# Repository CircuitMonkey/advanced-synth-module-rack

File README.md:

# advanced-synth-module-rack
ASMR -- Advanced Synth Module Rack System.  A modern alternative to Eurorack.

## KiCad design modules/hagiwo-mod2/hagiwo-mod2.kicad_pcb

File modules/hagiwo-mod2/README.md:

# Hagiwo Mod2 -- module for ASMR
This module is based on the highly versatile [Mod2 design](https://note.com/solder_state/n/nce8f7defcf98) by Japanese engineer "[Hagiwo](https://note.com/solder_state)".  The Mod2 can operate as a VCO, but can be programmed to masquerade as many types of dedicated drum instruments. This ASMR module is derived from the EuroRack version of their module.

## About
The Unison is based on the Arduino compatible RaspberryPi RP2350 chip. Here, we use the [Raspberry Pi Pico 2 - RP2350](https://www.adafruit.com/product/6006) processor module. Amazingly, it is touted as having a total BOM cost of about $9 in prototype form. Another benefit of the RP2350 based Mod2 module is that experimenters can study and modify the open source code that generates the functionality of the module.

## What is ASMR?
[ASMR -- Advanced Synth Module Rack System](https://github.com/CircuitMonkey/advanced-synth-module-rack).  A modern alternative to Eurorack.

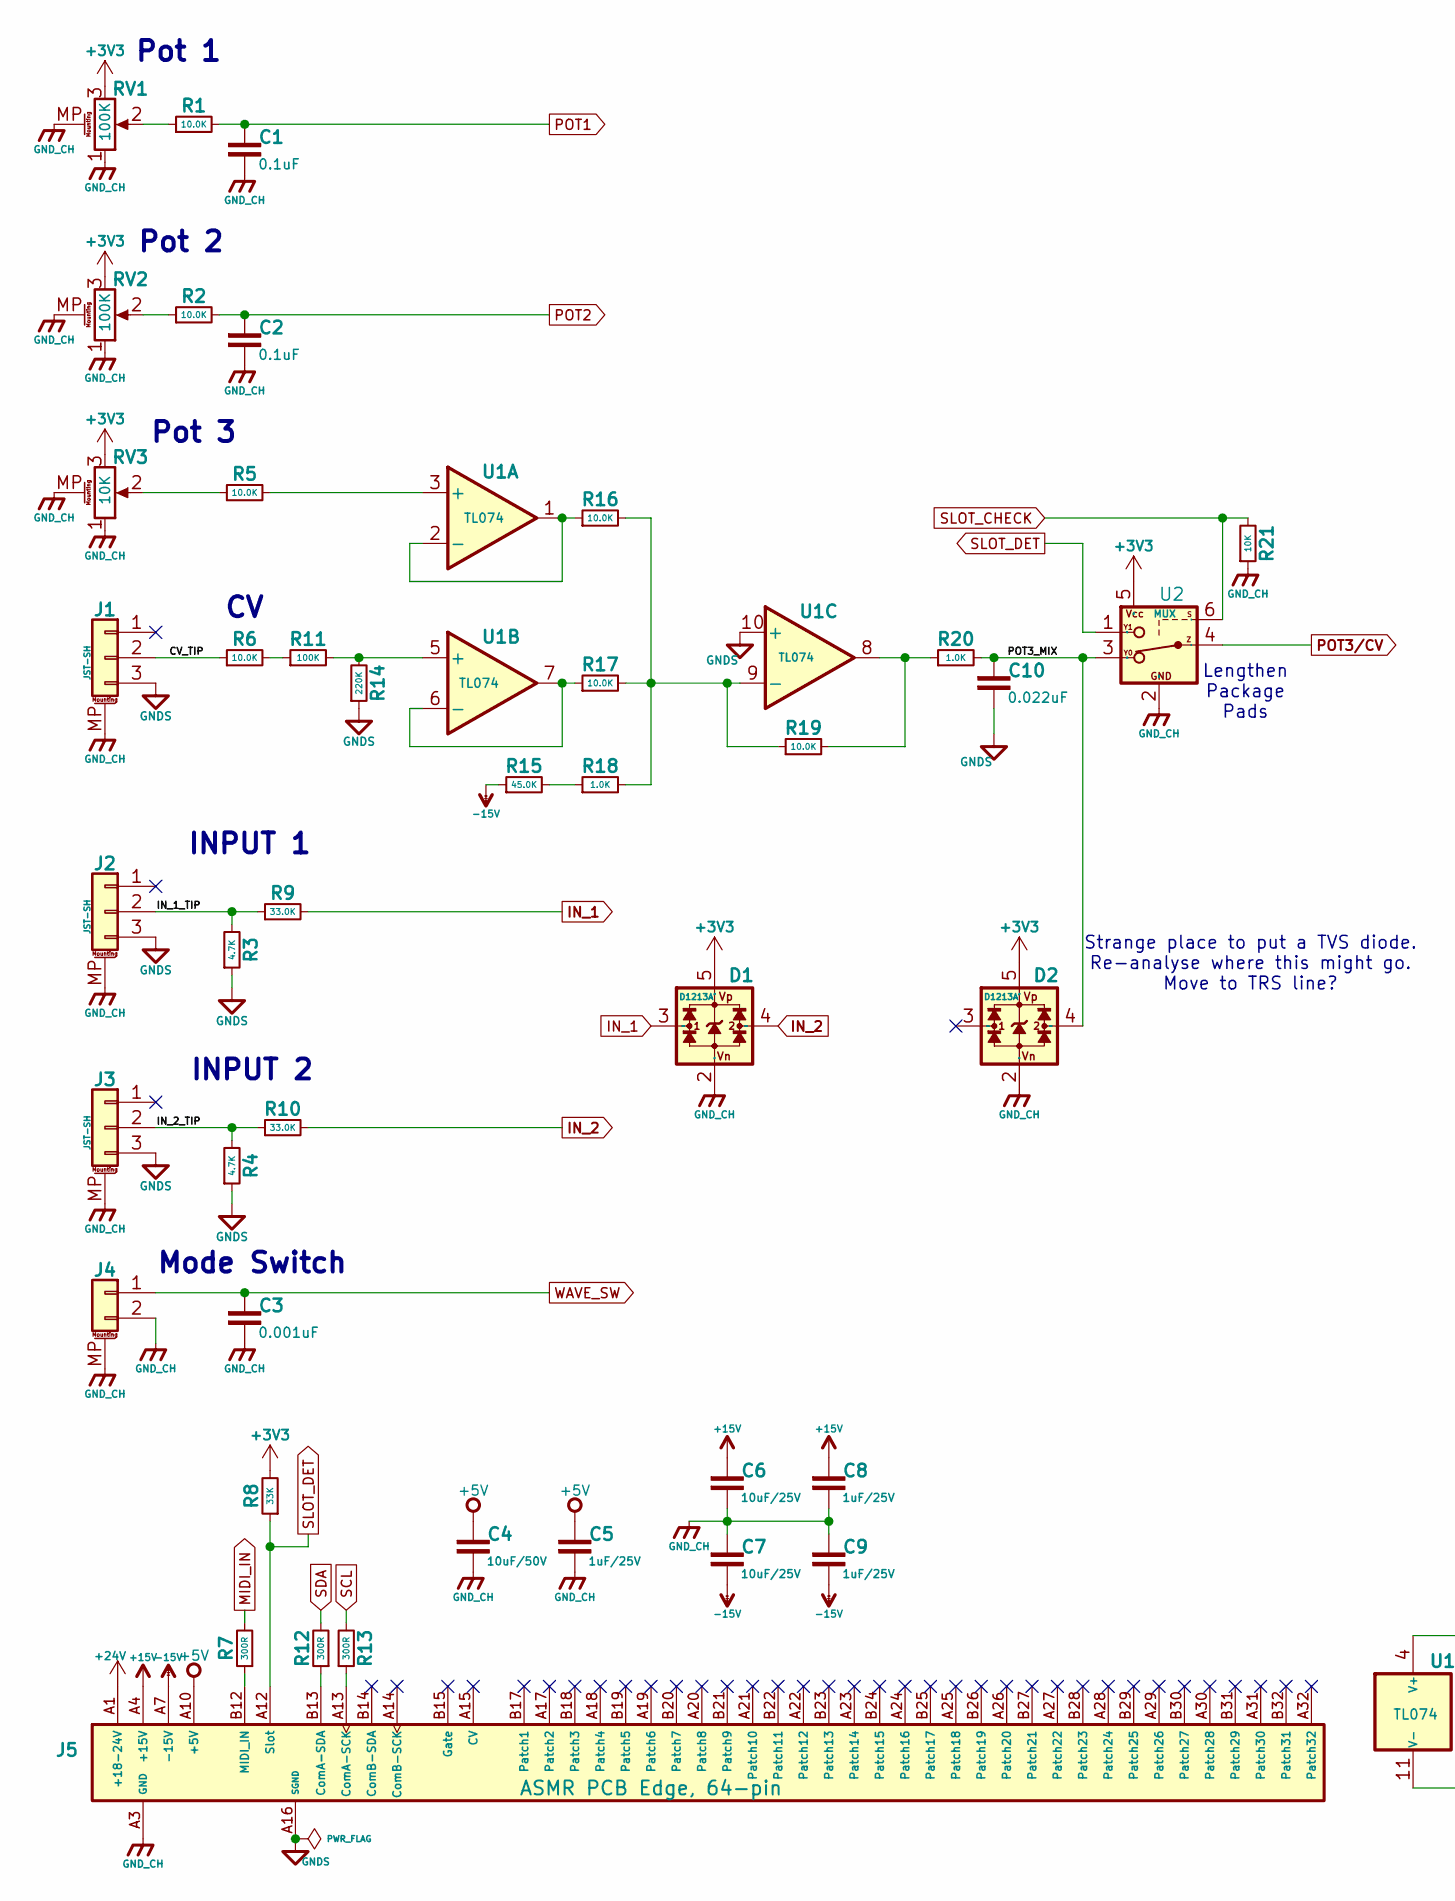
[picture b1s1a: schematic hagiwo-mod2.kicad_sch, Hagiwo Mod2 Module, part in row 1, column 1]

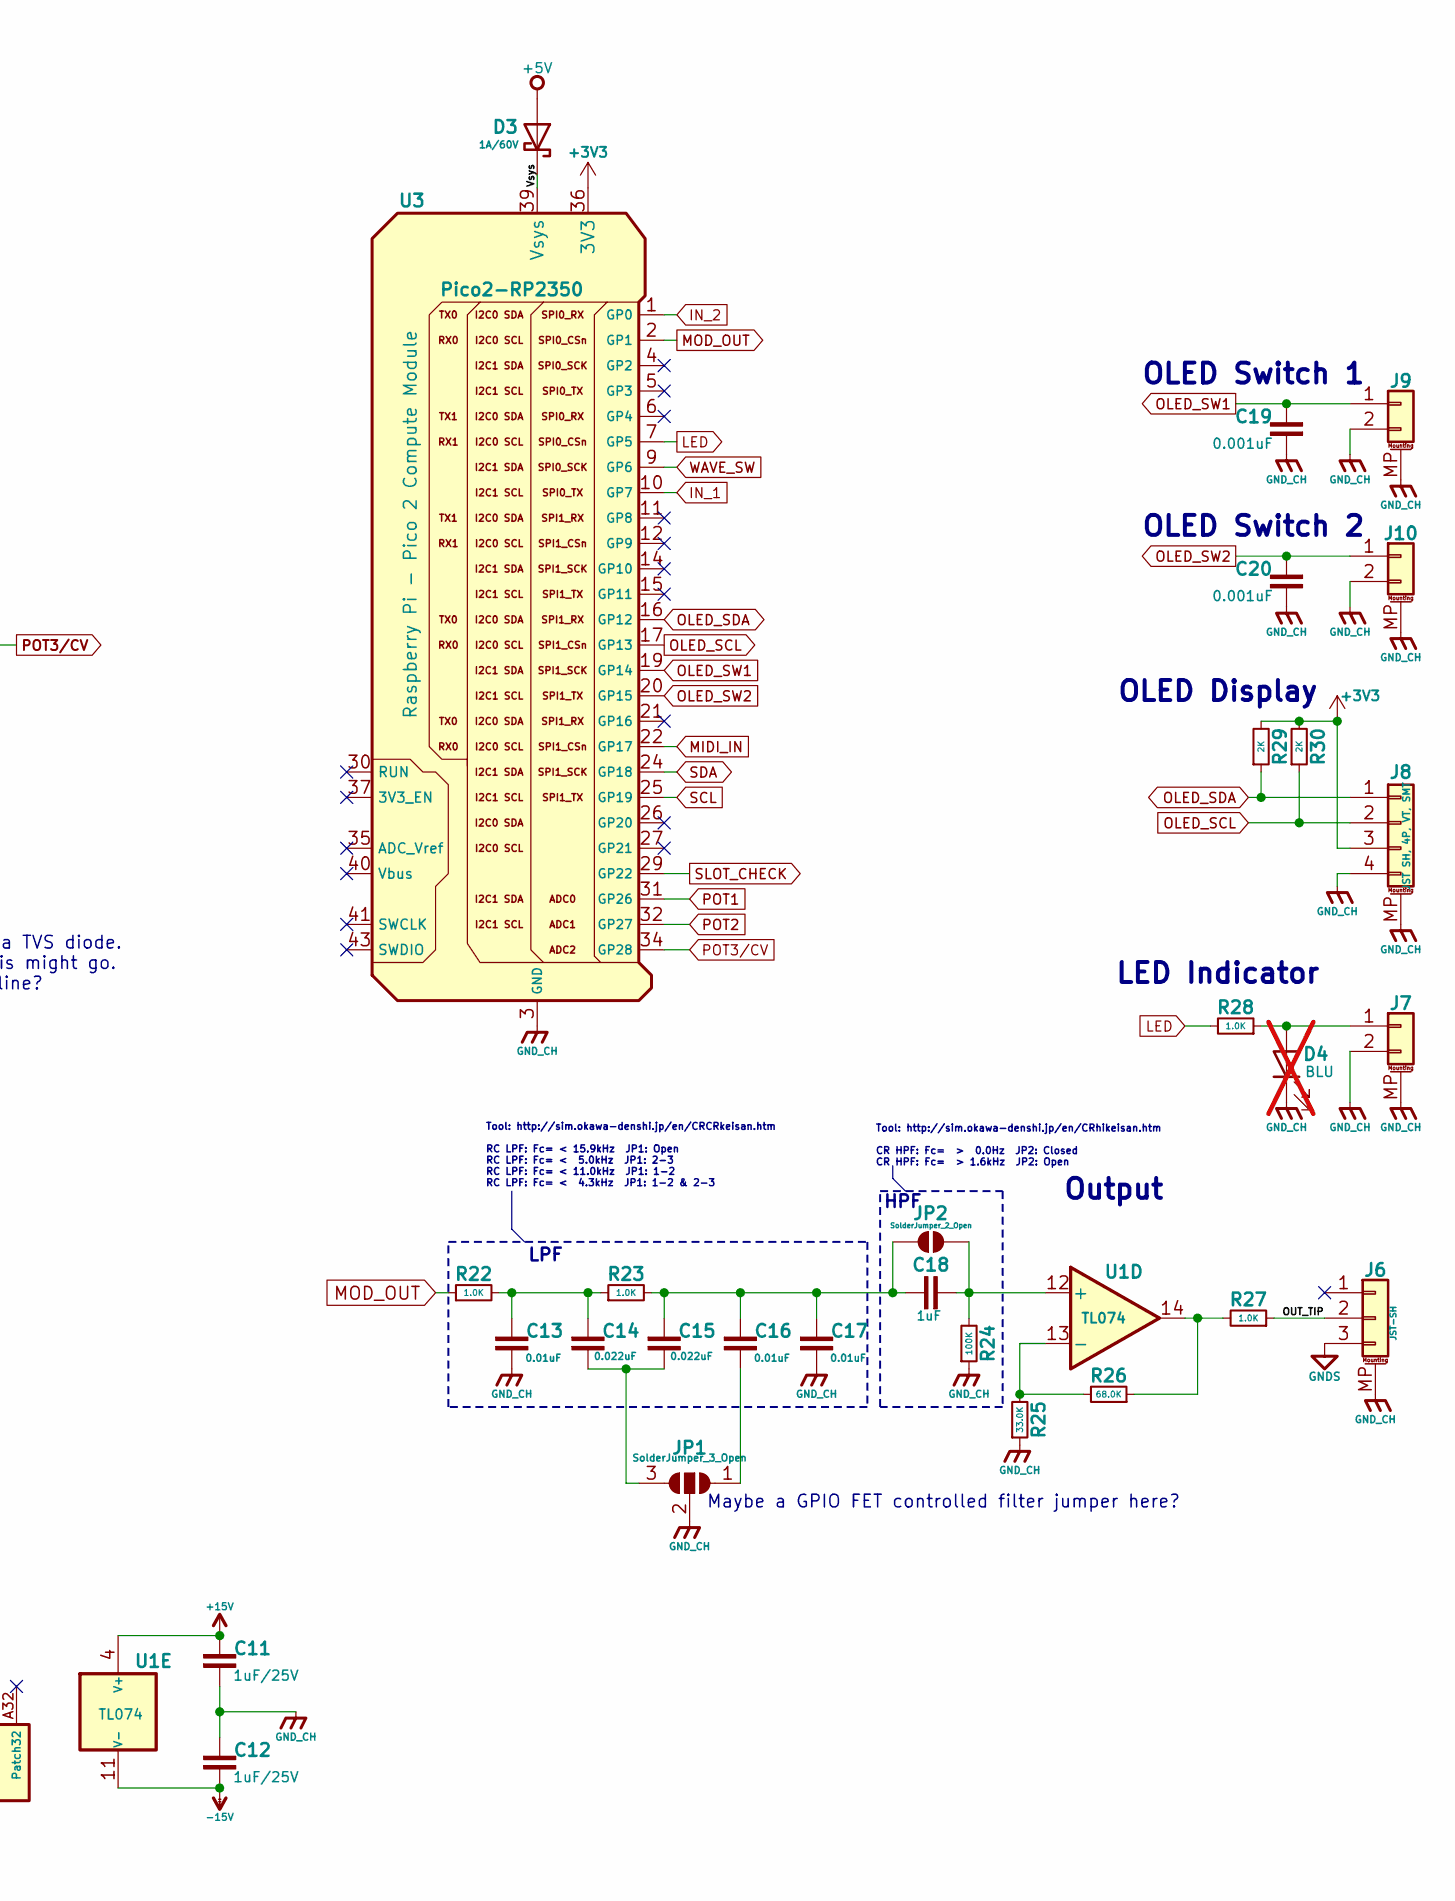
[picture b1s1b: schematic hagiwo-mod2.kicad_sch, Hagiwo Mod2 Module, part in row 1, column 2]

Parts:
C1, C2: 0.1uF; C_0603_1608Metric
C3, C19, C20: 0.001uF; C_0603_1608Metric
C4: 10uF/50V; C_0603_1608Metric
C5, C8, C9, C11, C12: 1uF/25V; C_0603_1608Metric
C6, C7: 10uF/25V; C_0603_1608Metric
C10, C14, C15: 0.022uF; C_0603_1608Metric
C13, C16, C17: 0.01uF; C_0603_1608Metric
C18: 1uF; C_0603_1608Metric
D1, D2: D1213A; SOT-25; MPN D1213A-02SM
D3: 1A/60V; D_SOD-123
D4: BLU; LED_0603_1608Metric; not fitted
J1, J2, J3, J6: JST-SH; JST_SH_BM03B-SRSS-TB_1x03-1MP_P1.00mm_Vertical
J4, J7, J9, J10: Conn_01x02_MountingPin; JST_SH_BM02B-SRSS-TB_1x02-1MP_P1.00mm_Vertical
J5: ASMR-Edge-64
J8: JST SH, 4P, VT, SMT; JST_SH_BM04B-SRSS-TB_1x04-1MP_P1.00mm_Vertical
JP1: SolderJumper_3_Open; SolderJumper-3_P1.3mm_Open_RoundedPad1.0x1.5mm_NumberLabels
JP2: SolderJumper_2_Open; SolderJumper-2_P1.3mm_Open_RoundedPad1.0x1.5mm
R1, R2, R5, R6, R16, R17, R19: 10.0K; R_0603_1608Metric
R3, R4: 4.7K; R_0603_1608Metric
R7, R12, R13: 300R; R_0603_1608Metric
R8: 33K; R_0603_1608Metric
R9, R10, R25: 33.0K; R_0603_1608Metric
R11, R24: 100K; R_0603_1608Metric
R14: 220K; R_0603_1608Metric
R15: 45.0K; R_0603_1608Metric
R18, R20, R22, R23, R27, R28: 1.0K; R_0603_1608Metric
R21: 10K; R_0603_1608Metric
R26: 68.0K; R_0603_1608Metric
R29, R30: 2K; R_0603_1608Metric
RV1: 100K; pot-thd-ra-11mm
RV2: 100K; pot-thd-ra-11mm; MPN A-5538
RV3: 10K; pot-thd-ra-11mm; MPN A-5533
U1: TL074; SO-14_3.9x8.65mm_P1.27mm; MPN TL074HIDR
U2: MUX; SOT-363_SC-70-6; MPN 74LVC1G3157GW-Q100
U3: Pico2-RP2350; RaspberryPi-Pico2

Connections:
+3V3: D1.5 (Vp), D2.5 (Vp), J8.3, R8.2, R29.2, R30.2, RV1.3, RV2.3, RV3.3, U2.5 (Vcc), U3.36 (3V3)
+5V: C4.1, C5.1, D3.2 (A), J5.A10 (+5V), J5.A11 (+5V), J5.B10 (+5V), J5.B11 (+5V)
+15V: C6.1, C8.1, C11.1, J5.A4 (+15V), J5.A5 (+15V), J5.B4 (+15V), J5.B5 (+15V), U1.4 (V+)
+24V: J5.A1 (+18-24V), J5.A2 (+18-24V), J5.B1 (+18-24V), J5.B2 (+18-24V)
-15V: C7.2, C9.2, C12.2, J5.A7 (-15V), J5.A8 (-15V), J5.B7 (-15V), J5.B8 (-15V), R15.1, U1.11 (V-)
/CV_TIP: J1.2, R6.1
/IN_1_TIP: J2.2, R3.2, R9.1
/IN_2_TIP: J3.2, R4.2, R10.1
/OUT_TIP: J6.2, R27.1
/POT3_MIX: C10.1, D2.4 (CH2), R20.2, U2.3 (Y0)
/Vsys: D3.1 (K), U3.39 (Vsys)
GNDS: C10.2, J1.3, J2.3, J3.3, J5.A16 (SGND), J5.B16 (SGND), J6.3, R3.1, R4.1, R14.1, U1.10 (+)
GND_CH: C1.2, C2.2, C3.2, C4.2, C5.2, C6.2, C7.1, C8.2, C9.1, C11.2, C12.1, C13.2, C17.2, C19.2, C20.2, D1.2 (Vn), D2.2 (Vn), D4.1 (K), J1.MP (MountPin), J2.MP (MountPin), J3.MP (MountPin), J4.2, J4.MP (MountPin), J5.A3 (GND), J5.A6 (GND), J5.A9 (GND), J5.B3 (GND), J5.B6 (GND), J5.B9 (GND), J6.MP (MountPin), J7.2, J7.MP (MountPin), J8.4, J8.MP (MountPin), J9.2, J9.MP (MountPin), J10.2, J10.MP (MountPin), JP1.2 (C), R21.1, R24.1, R25.1, RV1.1, RV1.MP (MountPin), RV2.1, RV2.MP (MountPin), RV3.1, RV3.MP (MountPin), U2.2 (GND), U3.3 (GND), U3.8 (GND), U3.13 (GND), U3.18 (GND), U3.23 (GND), U3.28 (GND), U3.33 (GND), U3.38 (GND), U3.42 (GND)
IN_1: D1.3 (CH1), R9.2, U3.10 (GP7)
IN_2: D1.4 (CH2), R10.2, U3.1 (GP0)
LED: R28.2, U3.7 (GP5)
MIDI_IN: R7.2, U3.22 (GP17)
MOD_OUT: R22.1, U3.2 (GP1)
unnamed: C13.1, C14.1, R22.2, R23.1
unnamed: D4.2 (A), J7.1, R28.1
unnamed: J5.A13 (ComA-SCK), R13.1
unnamed: J5.B13 (ComA-SDA), R12.1
unnamed: J5.B12 (MIDI_IN), R7.1
unnamed: C16.2, JP1.1 (A)
unnamed: C14.2, C15.2, JP1.3 (B)
unnamed: C15.1, C16.1, C17.1, C18.1, JP2.1 (A), R23.2
unnamed: C18.2, JP2.2 (B), R24.2, U1.12 (+)
unnamed: R1.1, RV1.2
unnamed: R2.1, RV2.2
unnamed: R5.1, RV3.2
unnamed: R6.2, R11.1
unnamed: R15.2, R18.1
unnamed: R19.2, R20.1, U1.8
unnamed: R26.1, R27.2, U1.14
unnamed: R5.2, U1.3 (+)
unnamed: R16.1, U1.1, U1.2 (-)
unnamed: R11.2, R14.2, U1.5 (+)
unnamed: R17.1, U1.6 (-), U1.7
unnamed: R16.2, R17.2, R18.2, R19.1, U1.9 (-)
unnamed: R25.2, R26.2, U1.13 (-)
OLED_SCL: J8.2, R30.1, U3.17 (GP13)
OLED_SDA: J8.1, R29.1, U3.16 (GP12)
OLED_SW1: C19.1, J9.1, U3.19 (GP14)
OLED_SW2: C20.1, J10.1, U3.20 (GP15)
POT1: C1.1, R1.2, U3.31 (GP26)
POT2: C2.1, R2.2, U3.32 (GP27)
POT3/CV: U2.4 (Z), U3.34 (GP28)
SCL: R13.2, U3.25 (GP19)
SDA: R12.2, U3.24 (GP18)
SLOT_CHECK: R21.2, U2.6 (S), U3.29 (GP22)
SLOT_DET: J5.A12 (Slot), R8.1, U2.1 (Y1)
WAVE_SW: C3.1, J4.1, U3.9 (GP6)

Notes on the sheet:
Tool: http://sim.okawa-denshi.jp/en/CRhikeisan.htm CR HPF: Fc= > 0.0Hz JP2: Closed CR HPF: Fc= > 1.6kHz JP2: Open
Pot 1
OLED Switch 2
Tool: http://sim.okawa-denshi.jp/en/CRCRkeisan.htm RC LPF: Fc= < 15.9kHz JP1: Open RC LPF: Fc= < 5.0kHz JP1: 2-3 RC LPF: Fc= < 11.0kHz JP1: 1-2 RC LPF: Fc= < 4.3kHz JP1: 1-2 & 2-3
HPF
LED Indicator
INPUT 2
OLED Switch 1
Lengthen Package Pads
Pot 3
Mode Switch
Strange place to put a TVS diode. Re-analyse where this might go. Move to TRS line?
Maybe a GPIO FET controlled filter jumper here?
INPUT 1
Pot 2
Output
LPF
OLED Display

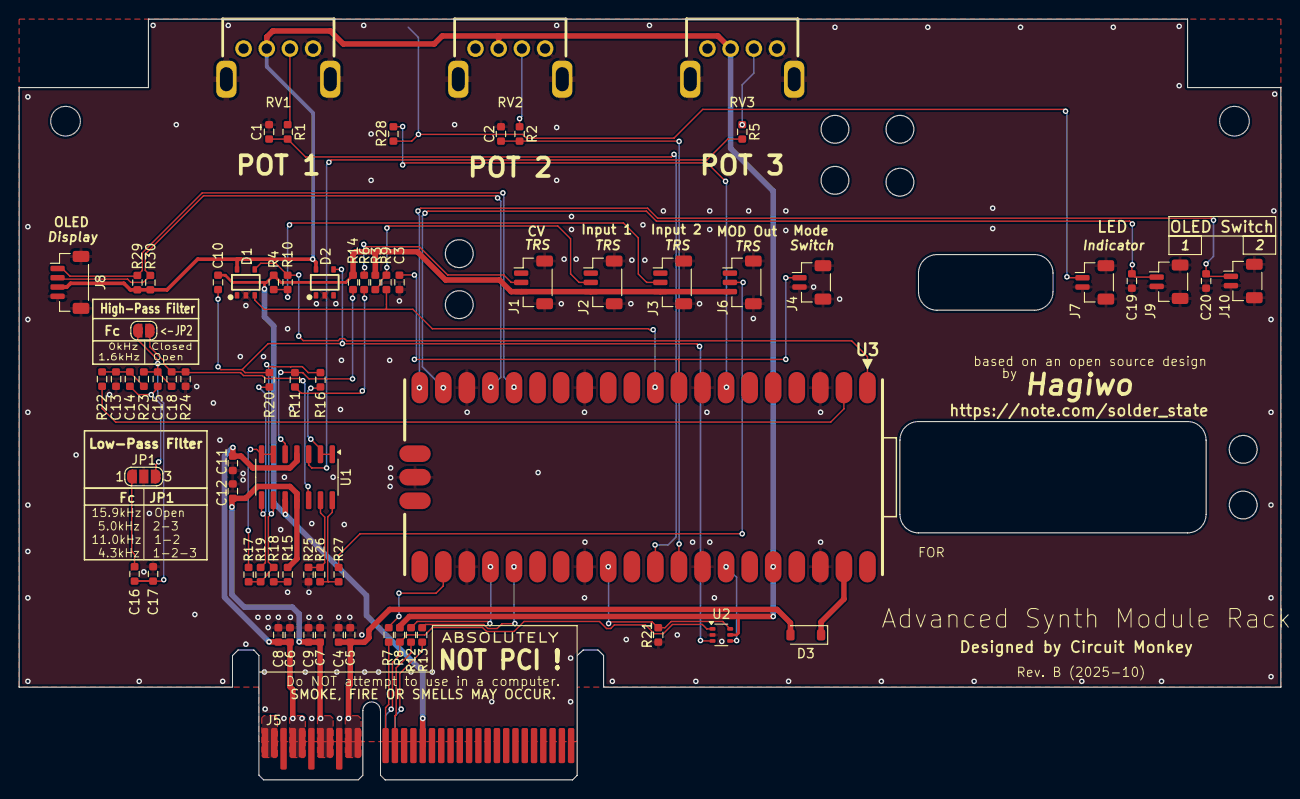
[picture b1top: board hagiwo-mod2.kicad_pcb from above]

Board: 2 copper layers, 136.0 x 82.0 mm, 72 parts (1 on the bottom side), 52 nets.

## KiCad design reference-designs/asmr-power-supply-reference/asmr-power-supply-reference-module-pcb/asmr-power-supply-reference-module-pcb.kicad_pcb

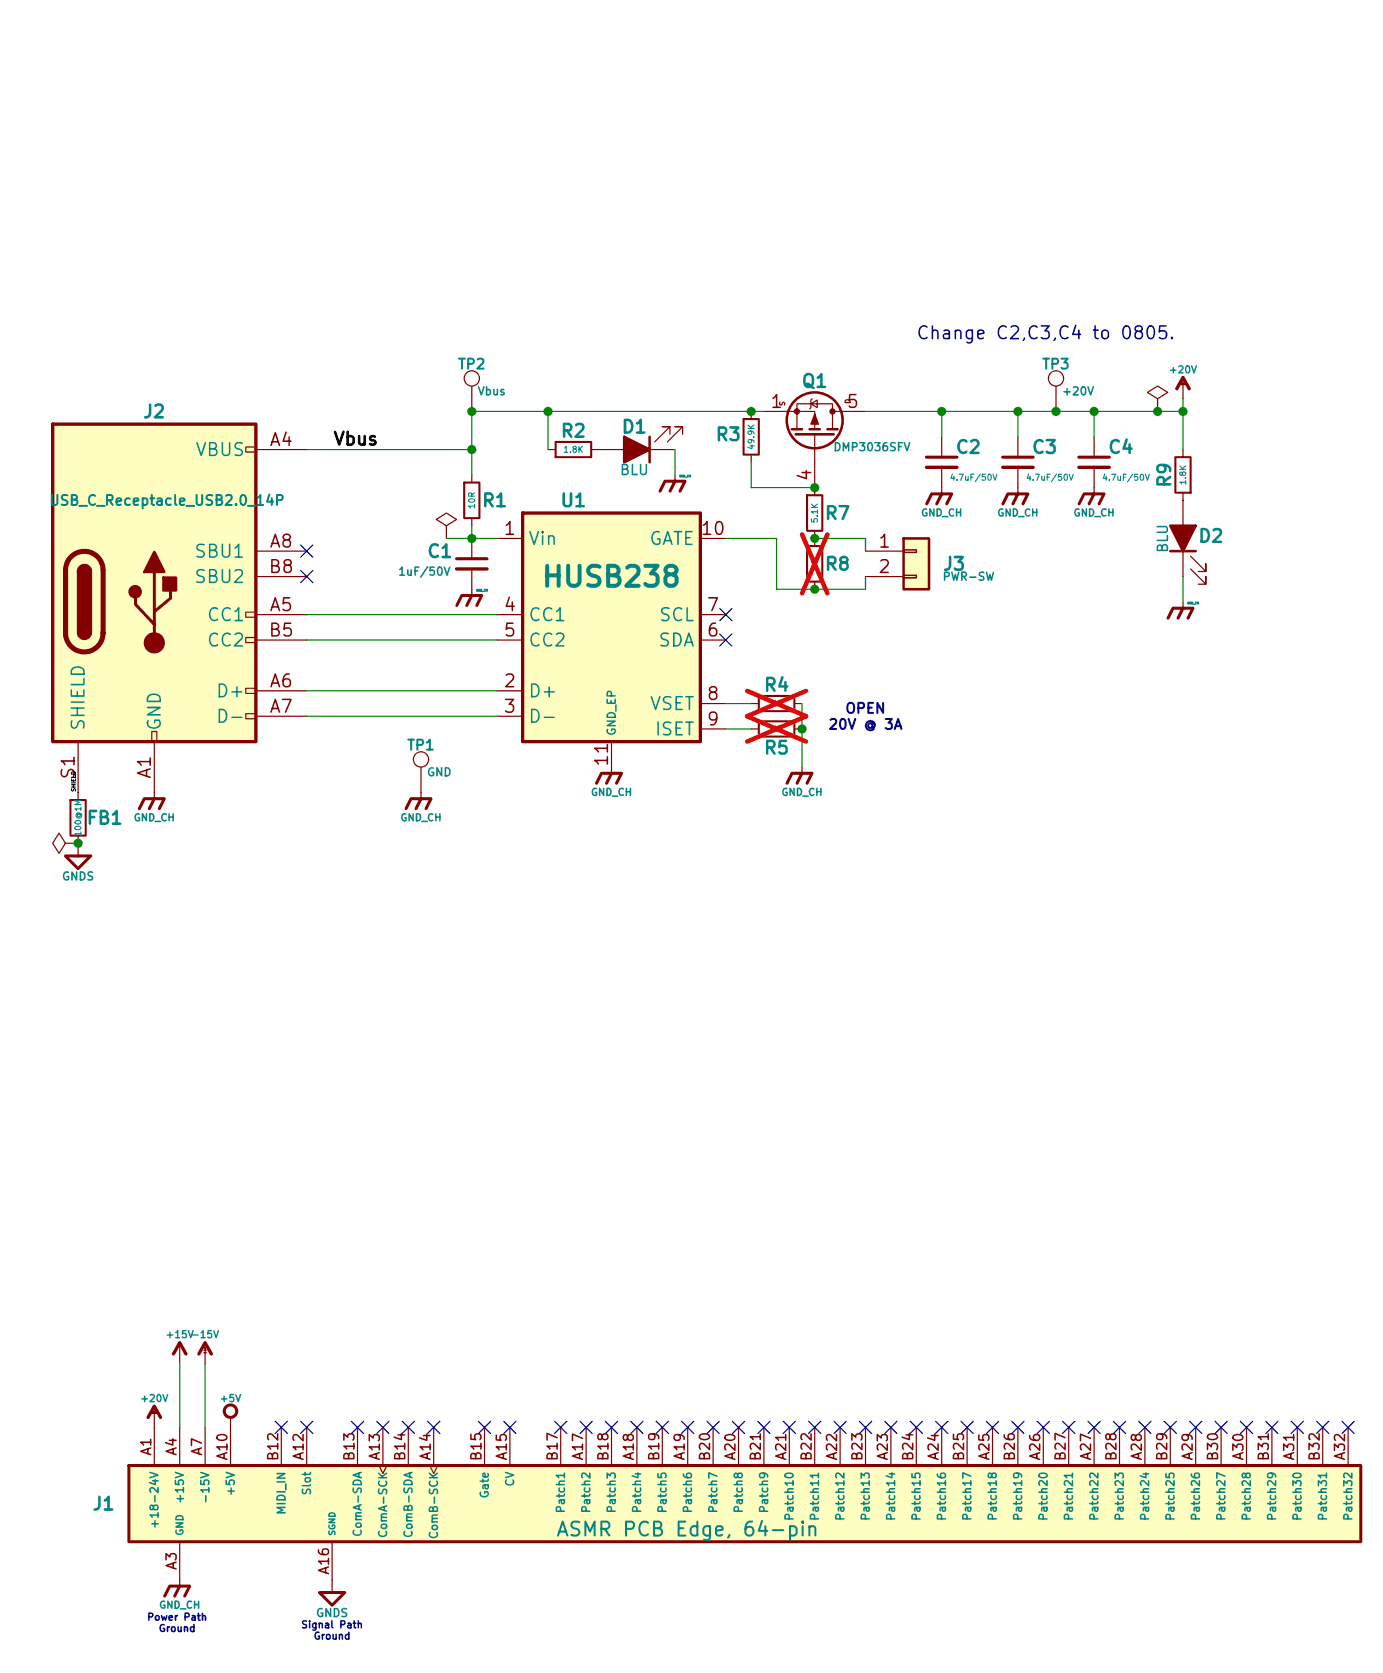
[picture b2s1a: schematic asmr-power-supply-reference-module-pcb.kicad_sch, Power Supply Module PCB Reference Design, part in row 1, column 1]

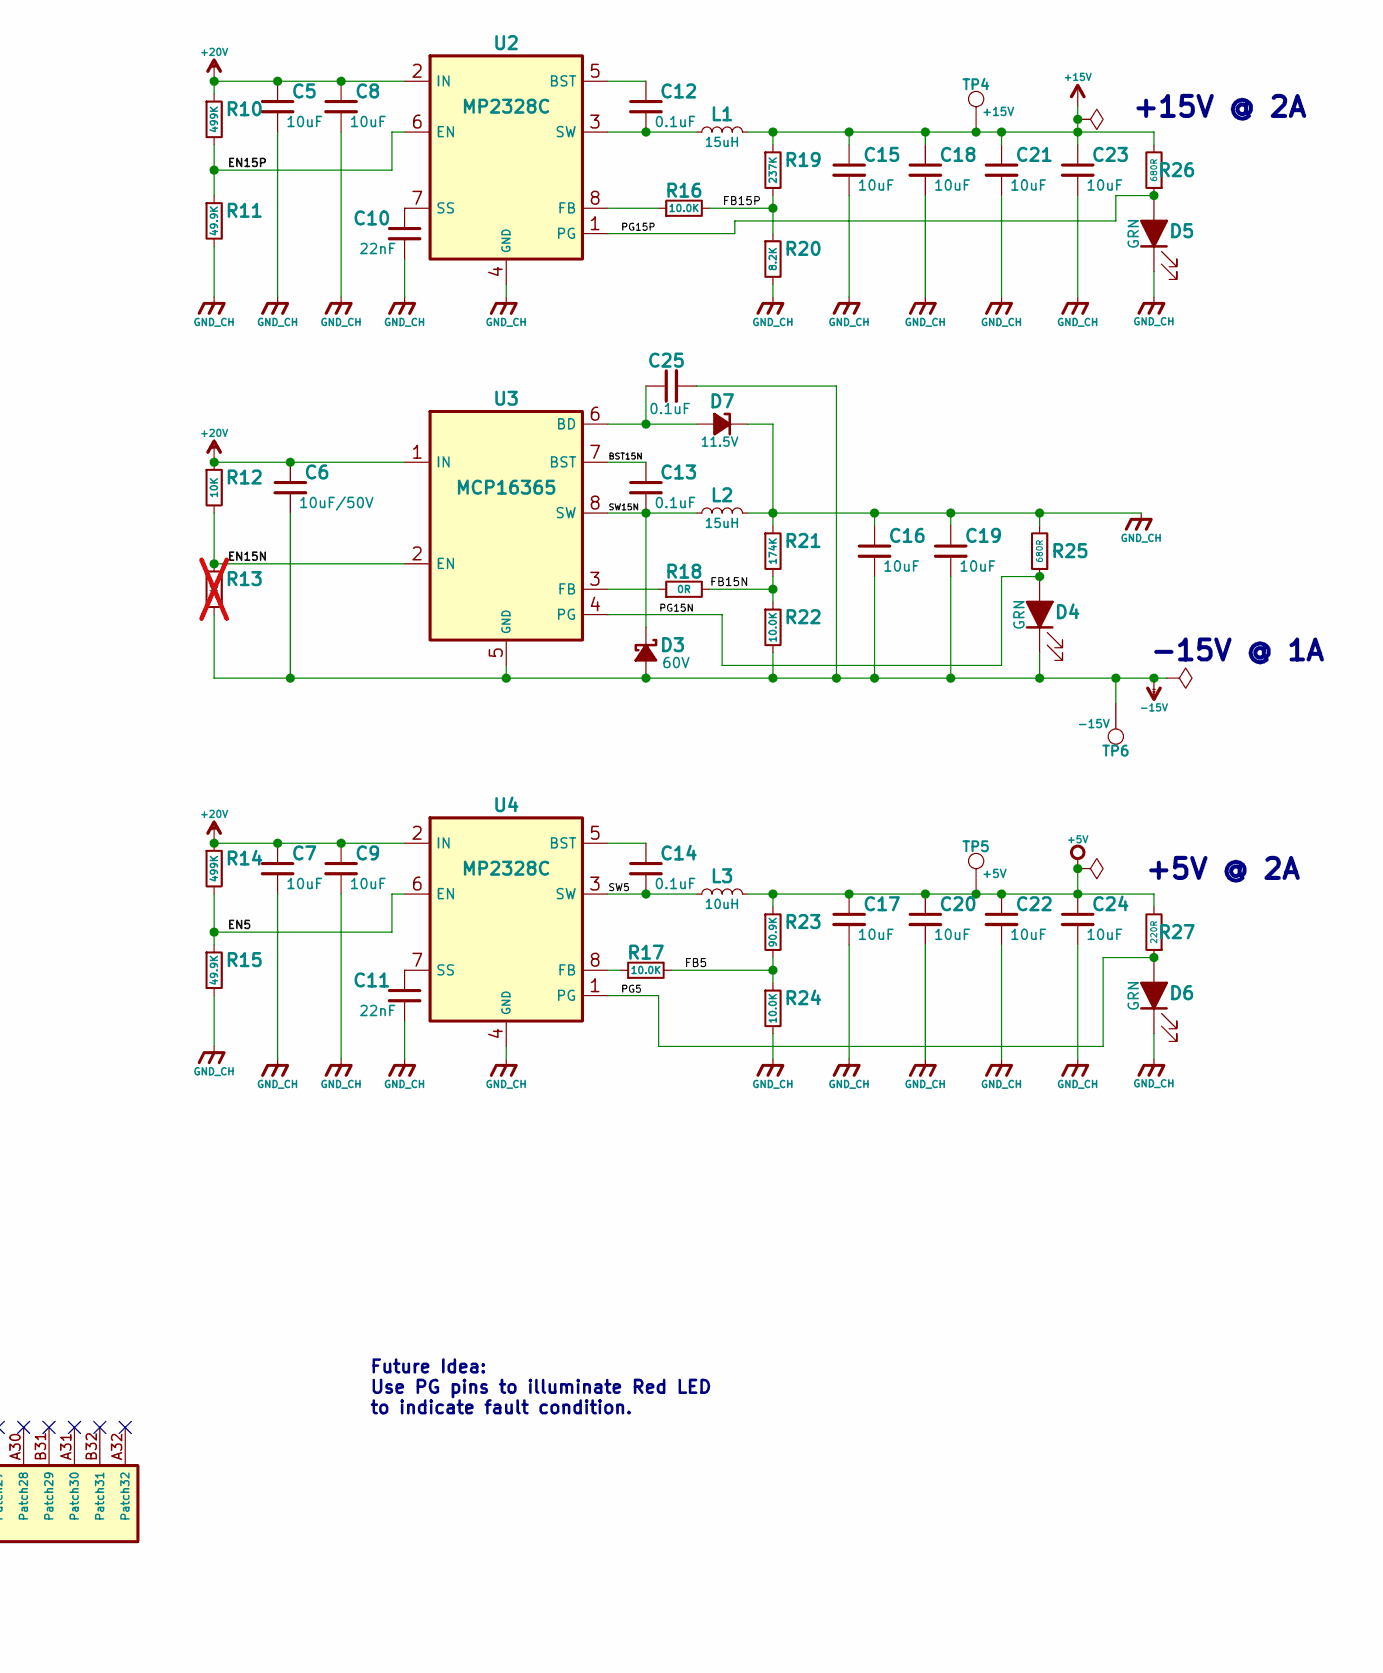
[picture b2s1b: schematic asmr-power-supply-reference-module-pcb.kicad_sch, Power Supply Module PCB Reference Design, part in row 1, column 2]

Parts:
C1: 1uF/50V; C_0603_1608Metric
C2, C3, C4: 4.7uF/50V; C_0603_1608Metric; MPN X7R, 1206, C3216X7R1E106M160AB
C5, C7, C8, C9: 10uF; C_1206_3216Metric; MPN X7S, 100V, TDK C5750X7S2A106M
C6: 10uF/50V; C_1206_3216Metric; MPN X7S, 100V, TDK C5750X7S2A106M
C10, C11: 22nF; C_0603_1608Metric
C12, C13, C14, C25: 0.1uF; C_0603_1608Metric
C15, C16, C17, C18, C19, C20, C21, C22, C23, C24: 10uF; C_1206_3216Metric; MPN X7R, 1206, C3216X7R1E106M160AB
D1, D2: BLU; LED_0603_1608Metric
D3: 60V; D_SMF; MPN SS2FH6
D4, D5, D6: GRN; LED_0603_1608Metric
D7: 11.5V; D_SOD-323_HandSoldering
FB1: 100@1M; R_0603_1608Metric
J1: ASMR-Edge-64
J2: USB_C_Receptacle_USB2.0_14P; USB_C_Receptacle_HCTL_HC-TYPE-C-16P-01A
J3: PWR-SW; JST_SH_BM02B-SRSS-TB_1x02-1MP_P1.00mm_Vertical
L1, L2: 15uH; SRN5040; MPN MPL-AL6060-150
L3: 10uH; SRN5040; MPN MPL-AL6060-100
Q1: DMP3036SFV; VSON-8_3.3x3.3mm_P0.65mm_NexFET; MPN DMP3036SFV
R1: 10R; R_0603_1608Metric
R2, R9: 1.8K; R_0603_1608Metric
R3, R11, R15: 49.9K; R_0603_1608Metric
R4, R5, R13: NS; R_0603_1608Metric; not fitted
R7: 5.1K; R_0603_1608Metric
R8: 0R; R_0603_1608Metric; not fitted
R10, R14: 499K; R_0603_1608Metric
R12: 10K; R_0603_1608Metric
R16, R17, R22, R24: 10.0K; R_0603_1608Metric
R18: 0R; R_0603_1608Metric
R19: 237K; R_0603_1608Metric
R20: 8.2K; R_0603_1608Metric
R21: 174K; R_0603_1608Metric
R23: 90.9K; R_0603_1608Metric
R25, R26: 680R; R_0603_1608Metric
R27: 220R; R_0603_1608Metric
TP1: GND; TestPoint_Keystone_5015_Micro_Mini
TP2: Vbus; TestPoint_Keystone_5015_Micro_Mini
TP3: +20V; TestPoint_Keystone_5015_Micro_Mini
TP4: +15V; TestPoint_Keystone_5015_Micro_Mini
TP5: +5V; TestPoint_Keystone_5015_Micro_Mini
TP6: -15V; TestPoint_Keystone_5015_Micro_Mini
U1: HUSB238; DFN-10-1EP_3x3mm_P0.5mm_EP1.65x2.38mm
U2, U4: MP2328C; SOT-583-8; MPN MP2328CGTL-Z
U3: MCP16365; DFN-8-1EP_3x3mm_P0.65mm_EP1.55x2.4mm; MPN MCP16365

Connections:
+5V: C17.1, C20.1, C22.1, C24.1, J1.A10 (+5V), J1.A11 (+5V), J1.B10 (+5V), J1.B11 (+5V), L3.2, R23.1, R27.2, TP5.1
+15V: C15.1, C18.1, C21.1, C23.1, J1.A4 (+15V), J1.A5 (+15V), J1.B4 (+15V), J1.B5 (+15V), L1.2, R19.1, R26.2, TP4.1
+20V: C2.1, C3.1, C4.1, C5.1, C6.1, C7.1, C8.1, C9.1, J1.A1 (+18-24V), J1.A2 (+18-24V), J1.B1 (+18-24V), J1.B2 (+18-24V), Q1.5 (S), Q1.6 (S), Q1.7 (S), Q1.8 (S), Q1.PAD (S), R9.2, R10.1, R12.1, R14.1, TP3.1, U2.2 (IN), U3.1 (IN), U4.2 (IN)
-15V: C6.2, C16.2, C19.2, C25.2, D3.2 (A), D4.1 (K), J1.A7 (-15V), J1.A8 (-15V), J1.B7 (-15V), J1.B8 (-15V), R13.2, R22.2, TP6.1, U3.5 (GND), U3.9 (EP)
/BST15N: C13.1, U3.7 (BST)
/EN5: R14.2, R15.1, U4.6 (EN)
/EN15N: R12.2, R13.1, U3.2 (EN)
/EN15P: R10.2, R11.1, U2.6 (EN)
/FB5: R17.2, R23.2, R24.1
/FB15N: R18.2, R21.2, R22.1
/FB15P: R16.2, R19.2, R20.1
/PG5: D6.2 (A), R27.1, U4.1 (PG)
/PG15N: D4.2 (A), R25.1, U3.4 (PG)
/PG15P: D5.2 (A), R26.1, U2.1 (PG)
/SHIELD: FB1.1, J2.S1 (SHIELD)
/SW5: C14.2, L3.1, U4.3 (SW)
/SW15N: C13.2, D3.1 (K), L2.1, U3.8 (SW)
/Vbus: J2.A4 (VBUS), J2.A9 (VBUS), J2.B4 (VBUS), J2.B9 (VBUS), Q1.1 (D), Q1.2 (D), Q1.3 (D), R1.1, R2.1, R3.1, TP2.1
GNDS: FB1.2, J1.A16 (SGND), J1.B16 (SGND)
GND_CH: C1.2, C2.2, C3.2, C4.2, C5.2, C7.2, C8.2, C9.2, C10.2, C11.2, C15.2, C16.1, C17.2, C18.2, C19.1, C20.2, C21.2, C22.2, C23.2, C24.2, C25.1, D1.1 (K), D2.1 (K), D5.1 (K), D6.1 (K), D7.1 (K), D7.2 (A), J1.A3 (GND), J1.A6 (GND), J1.A9 (GND), J1.B3 (GND), J1.B6 (GND), J1.B9 (GND), J2.A1 (GND), J2.A12 (GND), J2.B1 (GND), J2.B12 (GND), L2.2, R4.2, R5.2, R11.2, R15.2, R20.2, R21.1, R24.2, R25.2, TP1.1, U1.11 (GND_EP), U2.4 (GND), U3.6 (BD), U4.4 (GND)
unnamed: D1.2 (A), R2.2
unnamed: D2.2 (A), R9.1
unnamed: J2.A5 (CC1), U1.4 (CC1)
unnamed: J2.B5 (CC2), U1.5 (CC2)
unnamed: J3.1, R7.2, R8.1
unnamed: J3.2, R8.2, U1.10 (GATE)
unnamed: Q1.4 (G), R3.2, R7.1
unnamed: J2.A6 (D+), J2.B6 (D+), U1.2 (D+)
unnamed: J2.A7 (D-), J2.B7 (D-), U1.3 (D-)
unnamed: R5.1, U1.9 (ISET)
unnamed: R4.1, U1.8 (VSET)
unnamed: C1.1, R1.2, U1.1 (Vin)
unnamed: C12.1, U2.5 (BST)
unnamed: R16.1, U2.8 (FB)
unnamed: C10.1, U2.7 (SS)
unnamed: C12.2, L1.1, U2.3 (SW)
unnamed: R18.1, U3.3 (FB)
unnamed: C14.1, U4.5 (BST)
unnamed: R17.1, U4.8 (FB)
unnamed: C11.1, U4.7 (SS)

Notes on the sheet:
+5V @ 2A
Power Path Ground
Signal Path Ground
Future Idea: Use PG pins to illuminate Red LED to indicate fault condition.
-15V @ 1A
OPEN 20V @ 3A
Change C2,C3,C4 to 0805.
+15V @ 2A

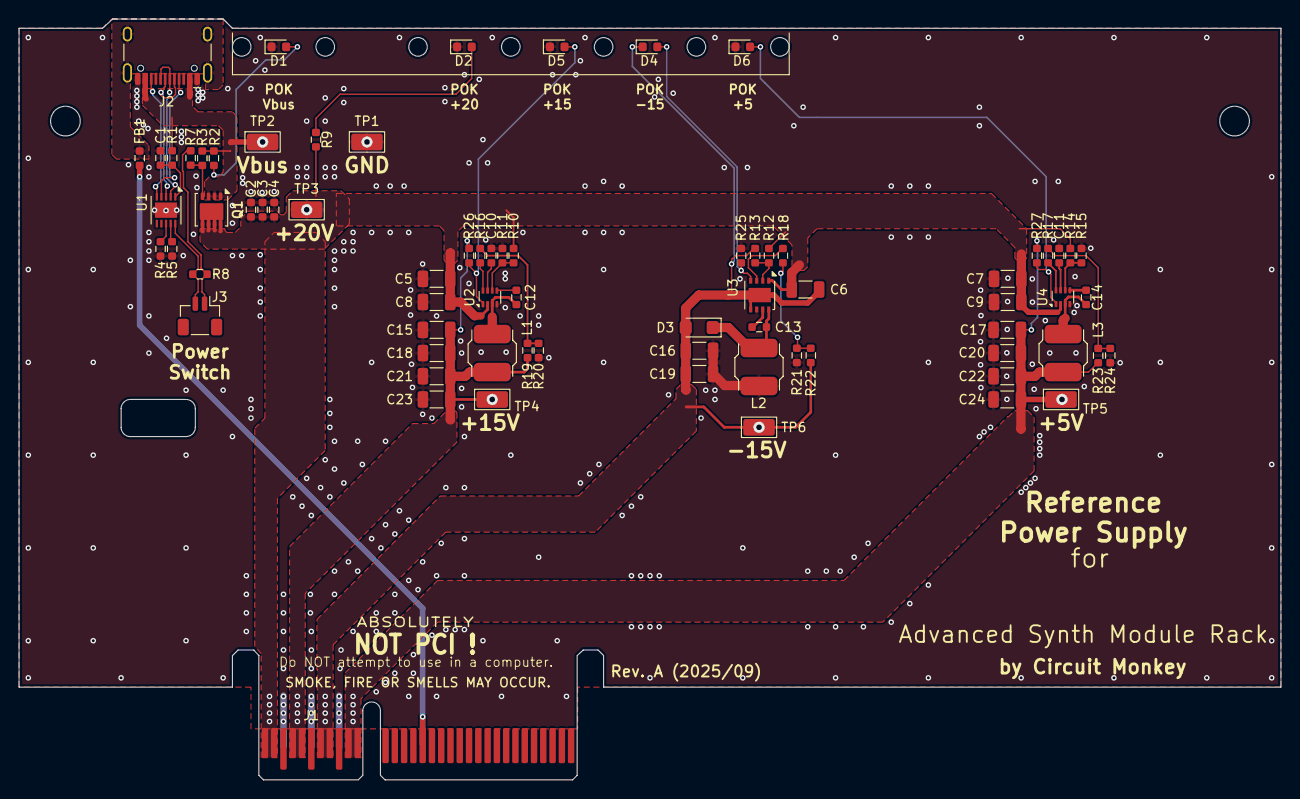
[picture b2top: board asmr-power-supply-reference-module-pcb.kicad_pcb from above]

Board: 2 copper layers, 136.0 x 82.0 mm, 74 parts (0 on the bottom side), 40 nets.
